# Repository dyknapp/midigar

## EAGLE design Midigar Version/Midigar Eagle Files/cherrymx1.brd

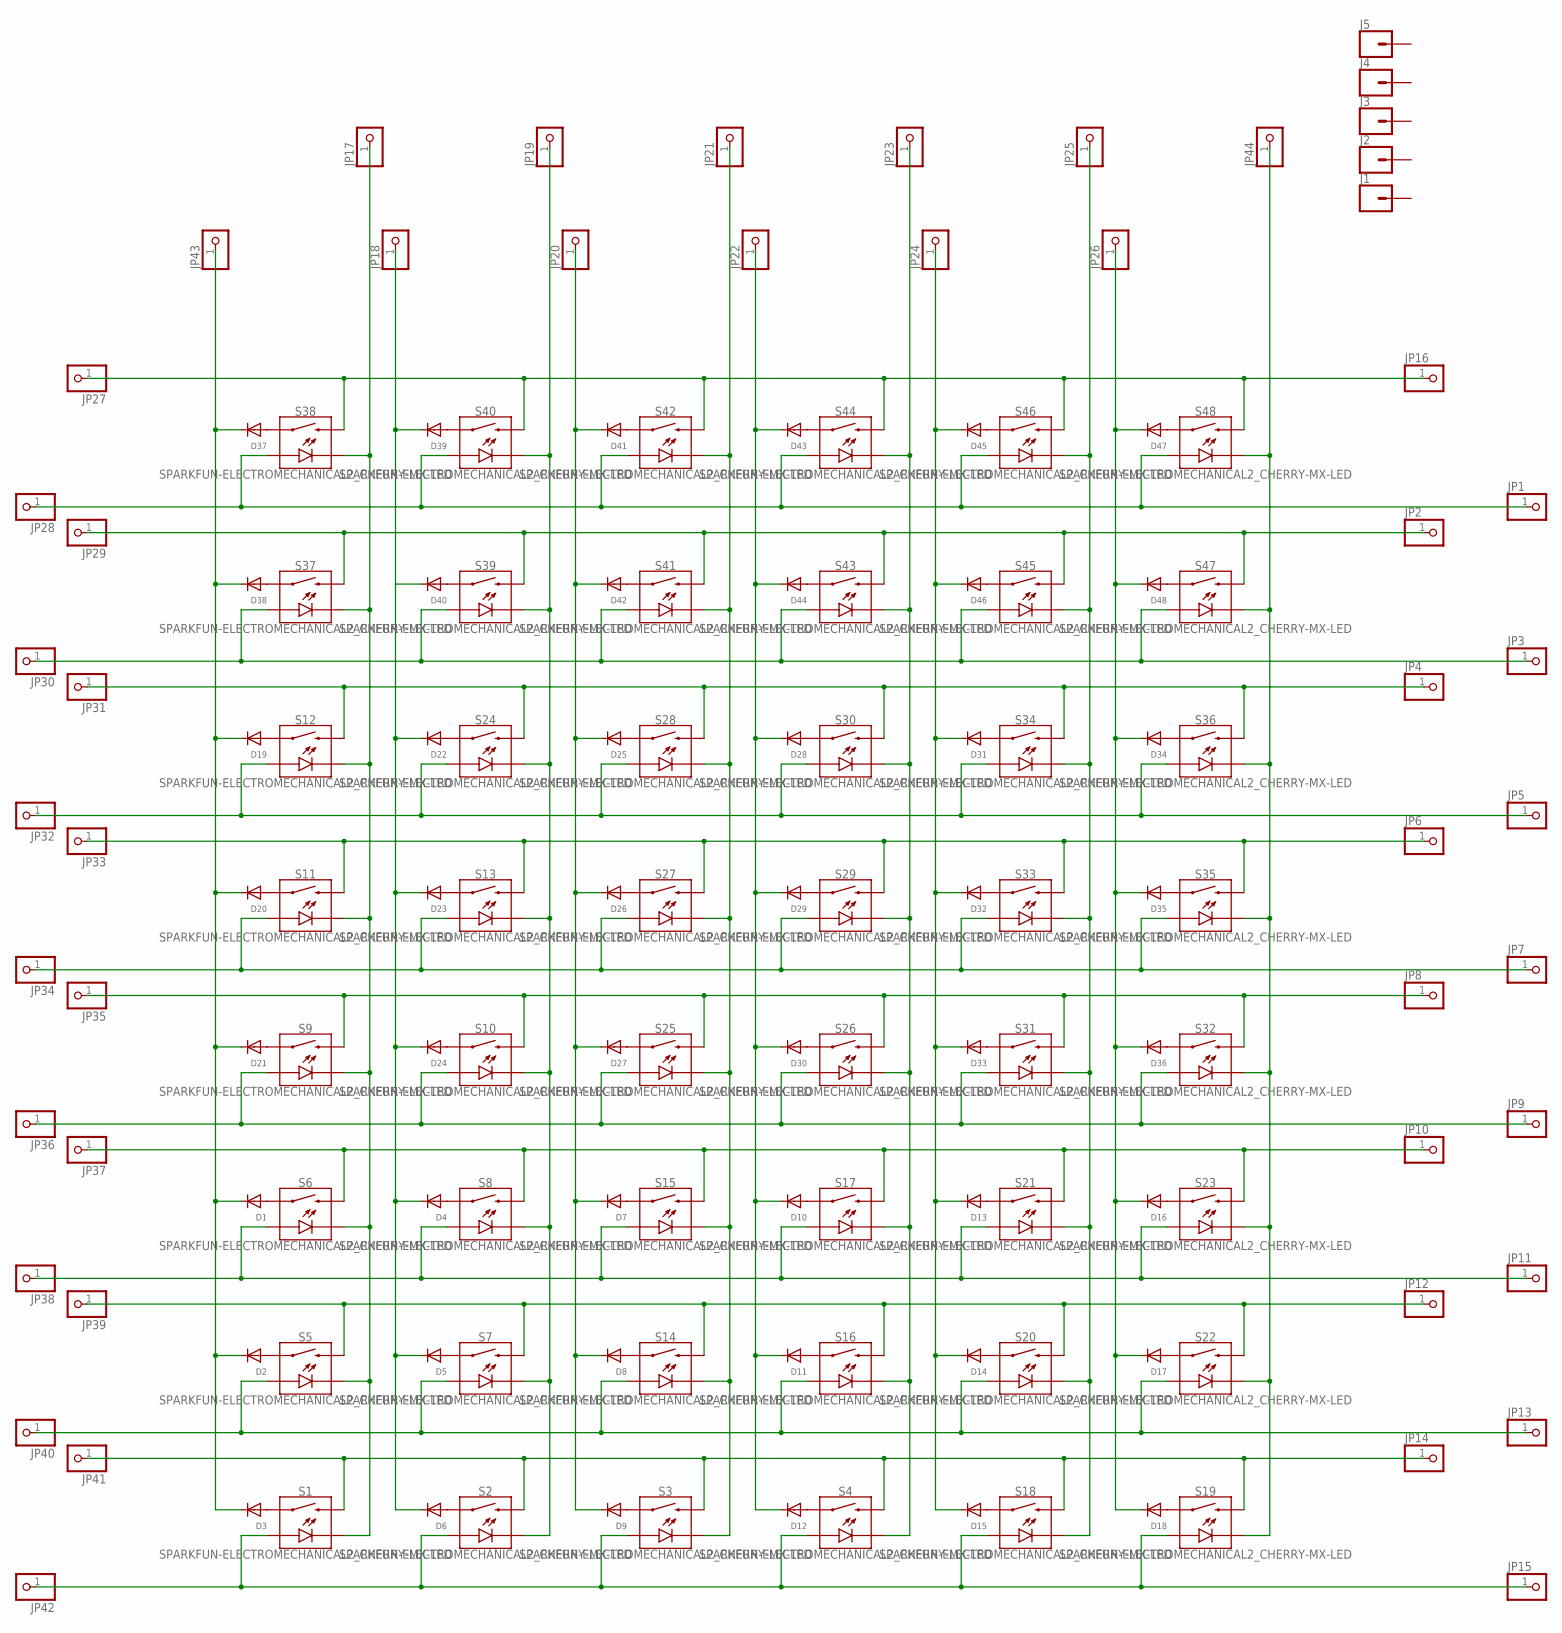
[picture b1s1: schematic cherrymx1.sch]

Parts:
D1, D2, D3, D4, D5, D6, D7, D8, D9, D10, D11, D12, D13, D14, D15, D16, D17, D18, D19, D20, D21, D22, D23, D24, D25, D26, D27, D28, D29, D30, D31, D32, D33, D34, D35, D36, D37, D38, D39, D40, D41, D42, D43, D44, D45, D46, D47, D48: DIODE_SOD-123FL; SOD-123FL
J1, J2, J3, J4, J5: CONN_01SMTSO-256-ET-0.165DIA; SMTSO-256-ET-0.165DIA
JP1, JP2, JP3, JP4, JP5, JP6, JP7, JP8, JP9, JP10, JP11, JP12, JP13, JP14, JP15, JP16, JP17, JP18, JP19, JP20, JP21, JP22, JP23, JP24, JP25, JP26, JP27, JP28, JP29, JP30, JP31, JP32, JP33, JP34, JP35, JP36, JP37, JP38, JP39, JP40, JP41, JP42, JP43, JP44: MICROBUILDER_HEADER-1X51X1_EDGESMT; MICROBUILDER_1X5_SMT
S1, S2, S3, S4, S5, S6, S7, S8, S9, S10, S11, S12, S13, S14, S15, S16, S17, S18, S19, S20, S21, S22, S23, S24, S25, S26, S27, S28, S29, S30, S31, S32, S33, S34, S35, S36, S37, S38, S39, S40, S41, S42, S43, S44, S45, S46, S47, S48: SPARKFUN-ELECTROMECHANICAL2_CHERRY-MX-LED

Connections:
unnamed: JP17.1, S1.K (C), S5.K (C), S6.K (C), S9.K (C), S11.K (C), S12.K (C), S37.K (C), S38.K (C)
unnamed: D1.A, S6.S1
unnamed: JP11.1, JP38.1, S6.A, S8.A, S15.A, S17.A, S21.A, S23.A
unnamed: JP13.1, JP40.1, S5.A, S7.A, S14.A, S16.A, S20.A, S22.A
unnamed: JP15.1, JP42.1, S1.A, S2.A, S3.A, S4.A, S18.A, S19.A
unnamed: D2.A, S5.S1
unnamed: D3.A, S1.S1
unnamed: D4.A, S8.S1
unnamed: D5.A, S7.S1
unnamed: D6.A, S2.S1
unnamed: D4.C, D5.C, D6.C, D22.C, D23.C, D24.C, D39.C, D40.C, JP18.1
unnamed: JP10.1, JP37.1, S6.S2, S8.S2, S15.S2, S17.S2, S21.S2, S23.S2
unnamed: JP12.1, JP39.1, S5.S2, S7.S2, S14.S2, S16.S2, S20.S2, S22.S2
unnamed: JP14.1, JP41.1, S1.S2, S2.S2, S3.S2, S4.S2, S18.S2, S19.S2
unnamed: JP21.1, S3.K (C), S14.K (C), S15.K (C), S25.K (C), S27.K (C), S28.K (C), S41.K (C), S42.K (C)
unnamed: JP23.1, S4.K (C), S16.K (C), S17.K (C), S26.K (C), S29.K (C), S30.K (C), S43.K (C), S44.K (C)
unnamed: D7.A, S15.S1
unnamed: D8.A, S14.S1
unnamed: D9.A, S3.S1
unnamed: D10.A, S17.S1
unnamed: D11.A, S16.S1
unnamed: D12.A, S4.S1
unnamed: D10.C, D11.C, D12.C, D28.C, D29.C, D30.C, D43.C, D44.C, JP22.1
unnamed: JP7.1, JP34.1, S11.A, S13.A, S27.A, S29.A, S33.A, S35.A
unnamed: JP9.1, JP36.1, S9.A, S10.A, S25.A, S26.A, S31.A, S32.A
unnamed: JP25.1, S18.K (C), S20.K (C), S21.K (C), S31.K (C), S33.K (C), S34.K (C), S45.K (C), S46.K (C)
unnamed: D19.A, S12.S1
unnamed: D20.A, S11.S1
unnamed: D13.A, S21.S1
unnamed: D14.A, S20.S1
unnamed: D15.A, S18.S1
unnamed: D16.A, S23.S1
unnamed: D17.A, S22.S1
unnamed: D18.A, S19.S1
unnamed: D13.C, D14.C, D15.C, D31.C, D32.C, D33.C, D45.C, D46.C, JP24.1
unnamed: D16.C, D17.C, D18.C, D34.C, D35.C, D36.C, D47.C, D48.C, JP26.1
unnamed: D21.A, S9.S1
unnamed: D22.A, S24.S1
unnamed: D23.A, S13.S1
unnamed: D24.A, S10.S1
unnamed: JP4.1, JP31.1, S12.S2, S24.S2, S28.S2, S30.S2, S34.S2, S36.S2
unnamed: JP6.1, JP33.1, S11.S2, S13.S2, S27.S2, S29.S2, S33.S2, S35.S2
unnamed: JP8.1, JP35.1, S9.S2, S10.S2, S25.S2, S26.S2, S31.S2, S32.S2
unnamed: JP5.1, JP32.1, S12.A, S24.A, S28.A, S30.A, S34.A, S36.A
unnamed: D25.A, S28.S1
unnamed: D26.A, S27.S1
unnamed: D27.A, S25.S1
unnamed: D28.A, S30.S1
unnamed: D29.A, S29.S1
unnamed: D30.A, S26.S1
unnamed: D7.C, D8.C, D9.C, D25.C, D26.C, D27.C, D41.C, D42.C, JP20.1
unnamed: D31.A, S34.S1
unnamed: D32.A, S33.S1
unnamed: D33.A, S31.S1
unnamed: D34.A, S36.S1
unnamed: D35.A, S35.S1
unnamed: D36.A, S32.S1
unnamed: JP19.1, S2.K (C), S7.K (C), S8.K (C), S10.K (C), S13.K (C), S24.K (C), S39.K (C), S40.K (C)
unnamed: JP1.1, JP28.1, S38.A, S40.A, S42.A, S44.A, S46.A, S48.A
unnamed: JP3.1, JP30.1, S37.A, S39.A, S41.A, S43.A, S45.A, S47.A
unnamed: D37.A, S38.S1
unnamed: D38.A, S37.S1
unnamed: D39.A, S40.S1
unnamed: D40.A, S39.S1
unnamed: D1.C, D2.C, D3.C, D19.C, D20.C, D21.C, D37.C, D38.C, JP43.1
unnamed: JP16.1, JP27.1, S38.S2, S40.S2, S42.S2, S44.S2, S46.S2, S48.S2
unnamed: JP2.1, JP29.1, S37.S2, S39.S2, S41.S2, S43.S2, S45.S2, S47.S2
unnamed: D41.A, S42.S1
unnamed: D42.A, S41.S1
unnamed: D43.A, S44.S1
unnamed: D44.A, S43.S1
unnamed: JP44.1, S19.K (C), S22.K (C), S23.K (C), S32.K (C), S35.K (C), S36.K (C), S47.K (C), S48.K (C)
unnamed: D45.A, S46.S1
unnamed: D46.A, S45.S1
unnamed: D47.A, S48.S1
unnamed: D48.A, S47.S1

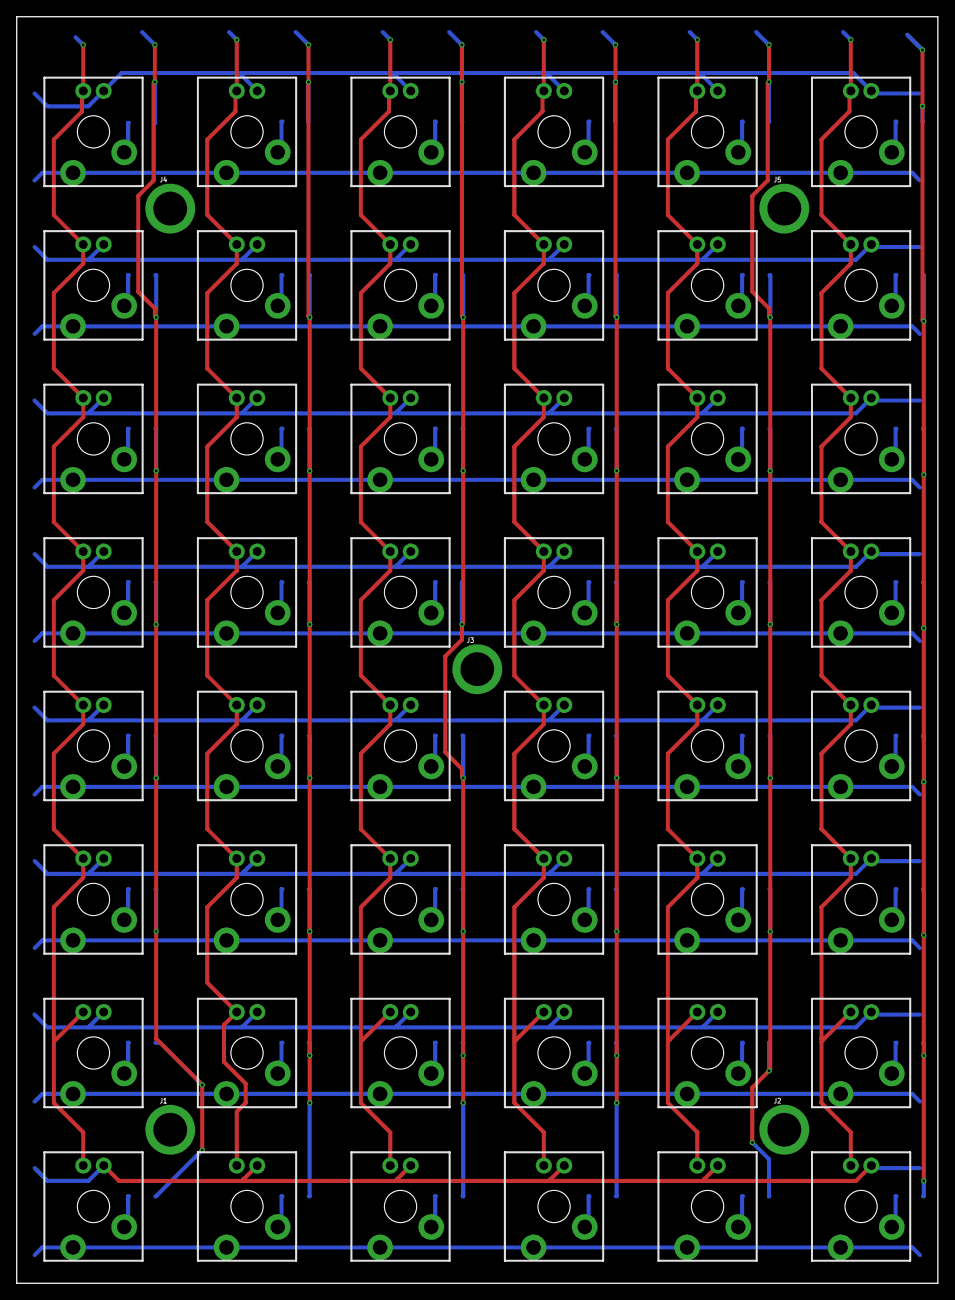
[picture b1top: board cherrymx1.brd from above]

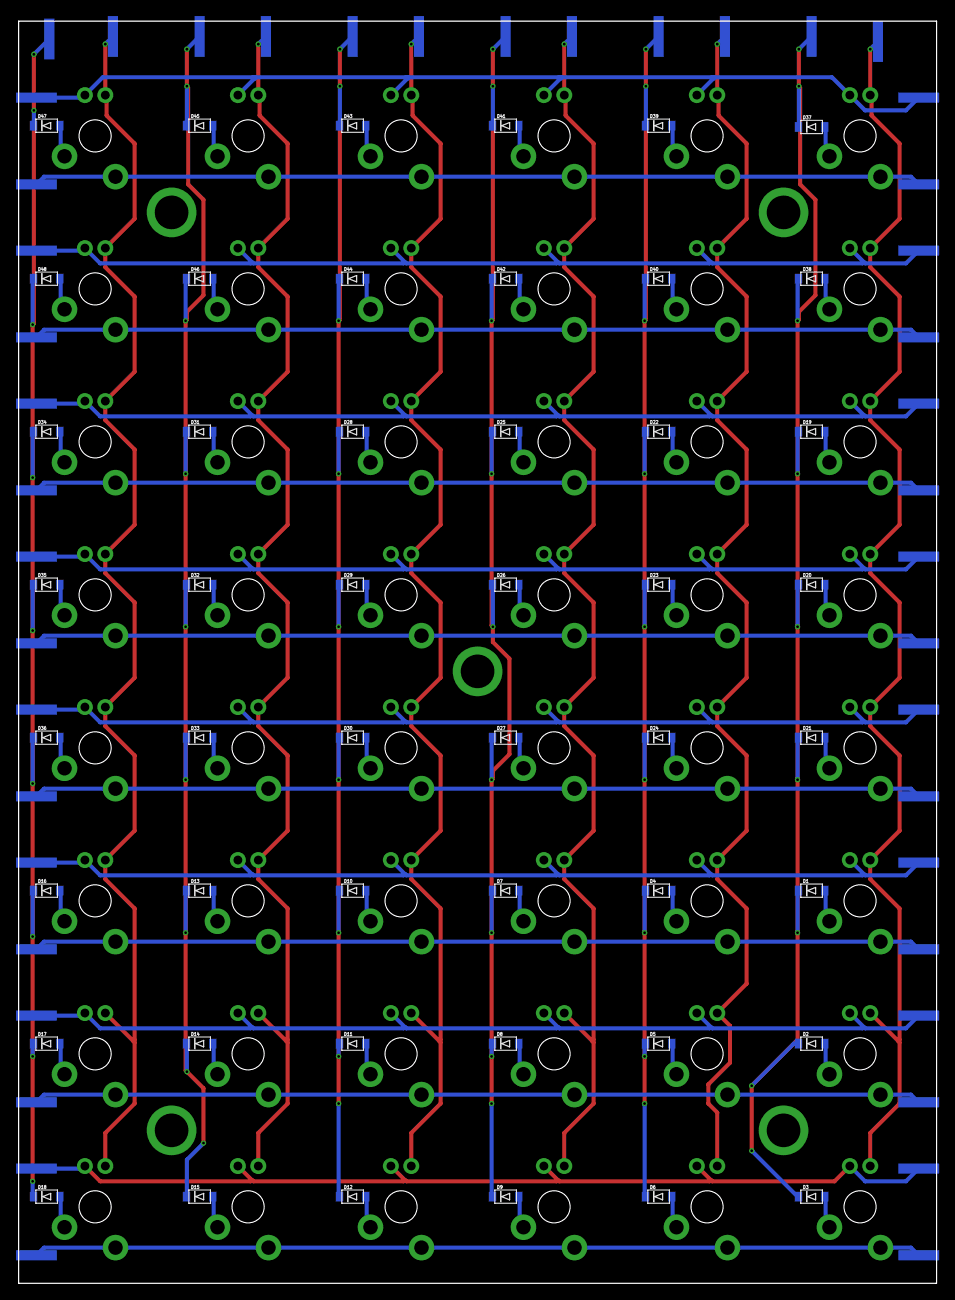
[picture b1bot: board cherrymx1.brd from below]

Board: 2 copper layers, 114.3 x 157.2 mm, 145 parts (92 on the bottom side), 76 nets.

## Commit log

2022-04-09 Getting Started
2022-05-18 OLED Display Working
    Includes library and basic code for OLED display
2022-05-18 Correct OLED Library Added
    Removed ssd1305 library and added ssd1306 library.
2022-06-20 Linking functionality

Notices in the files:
parts and their libraries:
SparkFun-Connectors: Licensing: Creative Commons ShareAlike 4.0 International - https://creativecommons.org/licenses/by-sa/4.0
